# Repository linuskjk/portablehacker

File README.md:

# Portable Hacker

Portable Hacker is a handheld device to test the security of WiFi networks and bluetooth.

## The project is designed to be:
- portable
- modular
- expandable
- easy to modify
- beginner-friendly Hardware

### Why does this exist?
- I created this project to learn how to design PCBs and how to implement communication between microcontrollers.

# Things you need

 - [ESP32 preferably with antenna support](https://de.aliexpress.com/item/1005006140555903.html)
 - [ESP8266 NodeMCU V3](https://de.aliexpress.com/item/1005006889833004.html)
 - [0.91" Oled display (I2C)](https://de.aliexpress.com/item/1005011907100931.html)
 - [Rotary encoder](https://no.rs-online.com/web/p/mechanical-rotary-encoders/1675389)
 - [PCB](pcb/final.kicad_pcb)
 - [2x100k Ohm Resistors](https://www.reichelt.de/de/de/shop/produkt/widerstand_metallschicht_100_kohm_0207_0_6_w_1_-11458)
 - [1x0.1uF capacitor](https://funduinoshop.com/bauelemente/passive-bauelemente/kondensatoren/keramikkondensator-0.1uf-104pf-50v)

# Tools you need
- Soldering Iron
- Solder wire
- 3D-Printer

# Installation

1. Assemble the PCB
2. Solder all components
3. Connect the OLED display
4. Connect the battery to the charger module. (B+/- to charger module and output of that to V+/GND pin) it is not on the pcb on purpose as this saves up a lot of space and still works perfectly fine (even better, as bc of this the battery placement is more flexible. Just click the charger module in the space on the bottom of the case. It fits perfectly and whithholds a lot of strenght.
5. Upload the firmware by uploading v1.ino to the esp32 and the handshakeV2_esp8266.ino to the ESP8266 you can do both by using Arduino IDE
6. Power on the device

## Firmware dependencies

### Arduino / ESP32 firmware

- Adafruit GFX Library
- Adafruit SSD1306
- ESP32Encoder
- BluetoothSerial, WiFi, and Wire are provided by the ESP32 Arduino core

### ESP8266 helper firmware

- ESP8266WiFi, user_interface.h, and the ESP8266 Arduino core

### Python capture tools

- Python 3.9+
- pyserial
- Optional: access to the serial port listed with `--port` or the `PORT` environment variable

The Python capture scripts now auto-detect a connected serial port when possible, but you can still pass a port manually if you want a specific device.

# Features

- ESP32 powered
- OLED UI with menu system
- Rotary encoder navigation
- Battery voltage monitoring
- WiFi network scanner
- Bluetooth scanner
- WiFi deauther
- Bluetooth Spammer
- Modular firmware architecture
- Rechargeable LiPo battery support
- Custom PCB
- 3D printable enclosure support

# Hardware

## Required Components

| Component | Description |
|---|---|
| ESP32 Dev Board | Preferably with external antenna support |
| 0.91\" OLED Display | I2C SSD1306 |
| Rotary Encoder | With push button |
| LiPo Battery | 3.7V rechargeable |
| TP4056 | LiPo charging module |
| 2x 100kΩ Resistors | Battery voltage divider |
| 0.1µF Capacitor | ADC smoothing |
| Custom PCB | Designed in KiCad |

# Battery Measurement Circuit

The battery voltage is measured using a voltage divider connected to GPIO34.

```text
VBAT ── R1 ──+── GPIO34
             |
             +── C1 ── GND
             |
             R2
             |
            GND
```
## Values

| Component | Value |
|---|---|
| R1 | 100kΩ |
| R2 | 100kΩ |
| C1 | 0.1µF |
# Pin Layout

## OLED Display

| OLED Pin | ESP32 Pin |
|---|---|
| SDA | GPIO21 |
| SCL | GPIO22 |
| VCC | 3.3V |
| GND | GND |

---

## Rotary Encoder

| Encoder Pin | ESP32 Pin |
|---|---|
| A | GPIO32 |
| B | GPIO33 |
| SW | GPIO25 |
| + | 3.3V |
| GND | GND |

---

## Battery Monitoring

| Signal | ESP32 Pin |
|---|---|
| BAT_SENSE | GPIO34 |

# Images

## BOM

| Reference | Qty | Value | Description | Price EUR | Pack Info | Link |
|---|---|---|---|---|---|---|
| C1 | 1 | 0.1uF | Unpolarized capacitor | 6.19 | 100 pcs | [Buy](https://amzn.eu/d/09888h7T) |
| R1 R2 | 2 | 100k | Resistors | 8.19 | 50 pcs | [Buy](https://amzn.eu/d/08NQdVll) |
| SW1 | 1 | EC11 Rotary Encoder | Rotary encoder with push button | 2.49 | 1 pc | [Buy](https://arduino-projekte.info/products/ec11-rotary-encoder?srsltid=AfmBOoql9EZHMg89JvVqM8fnVPwwvv0NLhGciYfBVo8YLQL4ypCRxuZV) |
| U2 | 1 | SSD1306 0.91-inch OLED | I2C OLED display 128x32 | 1.35 | 1 pc | [Buy](https://de.aliexpress.com/item/1005011907100931.html) |
| U3 | 1 | ESP32-DevKitC | ESP32 development board | 2.99 | 1 pc | [Buy](https://de.aliexpress.com/item/1005006140555903.html) |
| U4 | 1 | DC-DC Buck Boost 600mA | Step-up/down power module | 0.99 | 1 pc | [Buy](https://de.aliexpress.com/item/1005008878997808.html) |
| U5 | 1 | TP4056 Type-C Charger Module | Li-ion charging module | 0.99 | 1 pc | [Buy](https://de.aliexpress.com/item/1005011840928544.html) |
| U6 | 1 | ESP8266 NodeMCU V3 | WiFi development board | 2.70 | 1 pc | [Buy](https://de.aliexpress.com/item/1005006889833004.html) |
| Battery | 1 | 654060 Li-Po 2000mAh | Lithium polymer battery | 9.90 | 1 pc | [Buy](https://de.aliexpress.com/item/1005011549440731.html) |
| Charger Module | 1 | TP4057 | USB-C charging module | 3.83 | 1 pc | [Buy](https://de.aliexpress.com/item/1005010764961491.html) |

### Total Cost
- Full pack prices: **39.62 EUR**
- Actual project usage cost: **25.46 EUR**

## Authors

- [@linuskjk](https://www.github.com/linuskjk)

## License

See [LICENSE](LICENSE) for the full text.

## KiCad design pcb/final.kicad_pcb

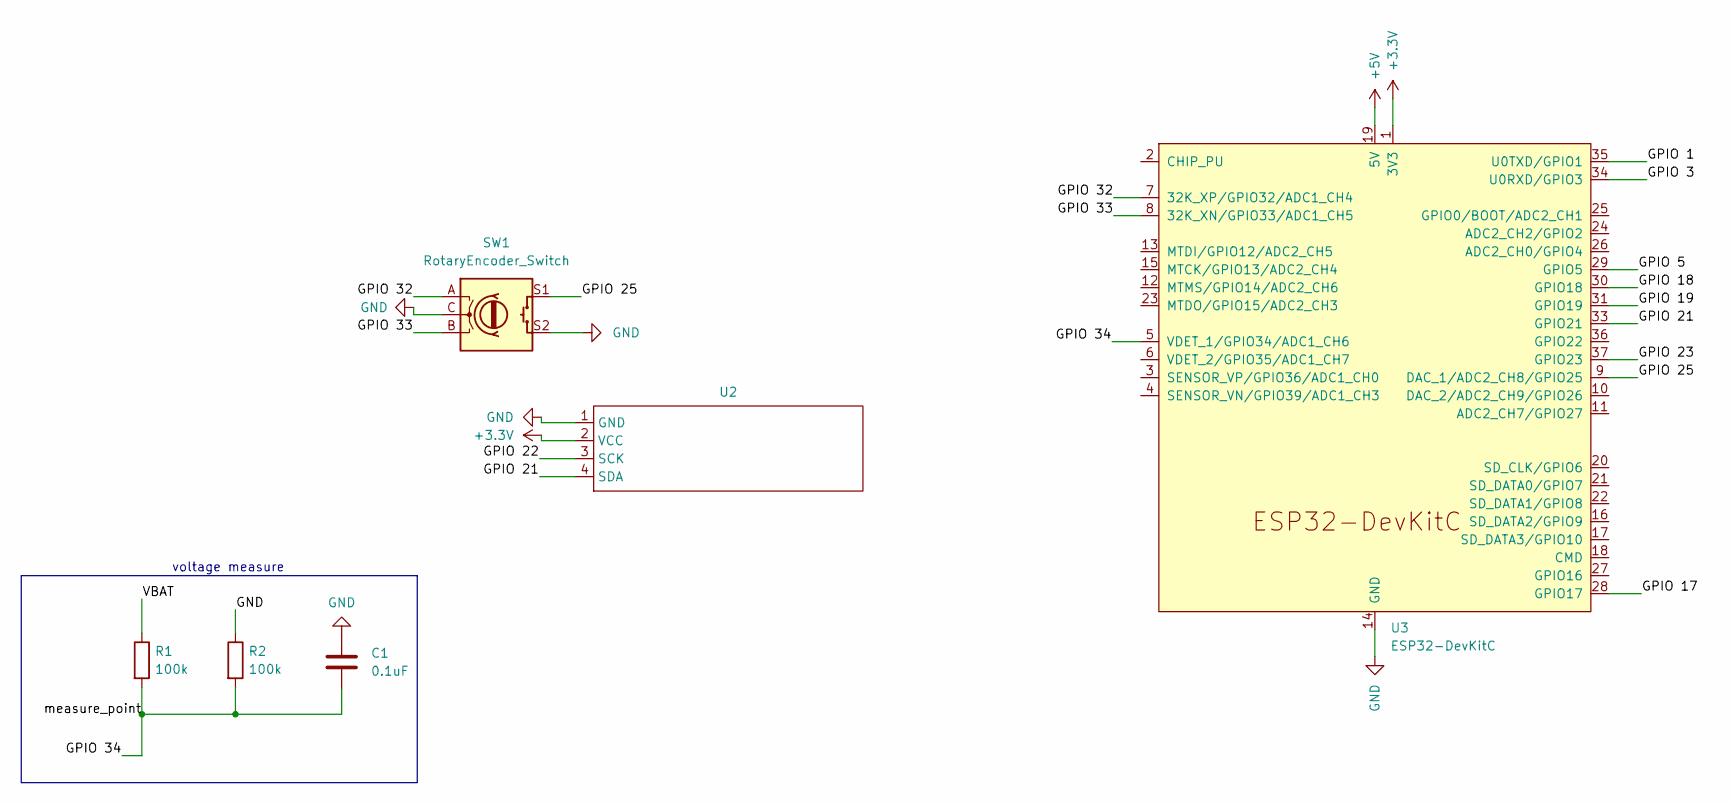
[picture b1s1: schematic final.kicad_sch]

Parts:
C1: 0.1uF; C_Disc_D5.0mm_W2.5mm_P5.00mm
R1, R2: 100k; R_Axial_DIN0207_L6.3mm_D2.5mm_P7.62mm_Horizontal
SW1: RotaryEncoder_Switch; RotaryEncoder_Alps_EC12E-Switch_Vertical_H20mm_CircularMoun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
U2: Untitled
U3: ESP32-DevKitC

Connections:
+3.3V: U2.2 (VCC), U3.1 (3V3)
+5V: U3.19 (5V)
/GPIO 1: U3.35 (U0TXD/GPIO1)
/GPIO 3: U3.34 (U0RXD/GPIO3)
/GPIO 5: U3.29 (GPIO5)
/GPIO 17: U3.28 (GPIO17)
/GPIO 18: U3.30 (GPIO18)
/GPIO 19: U3.31 (GPIO19)
/GPIO 21: U2.4 (SDA), U3.33 (GPIO21)
/GPIO 22: U2.3 (SCK), U3.36 (GPIO22)
/GPIO 23: U3.37 (GPIO23)
/GPIO 25: SW1.S1, U3.9 (DAC_1/ADC2_CH8/GPIO25)
/GPIO 32: SW1.A, U3.7 (32K_XP/GPIO32/ADC1_CH4)
/GPIO 33: SW1.B, U3.8 (32K_XN/GPIO33/ADC1_CH5)
/GPIO 34: C1.2, R1.2, R2.2, U3.5 (VDET_1/GPIO34/ADC1_CH6)
/VBAT: R1.1
GND: C1.1, R2.1, SW1.C, SW1.S2, U2.1 (GND), U3.14 (GND), U3.32 (GND), U3.38 (GND)

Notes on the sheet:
voltage measure

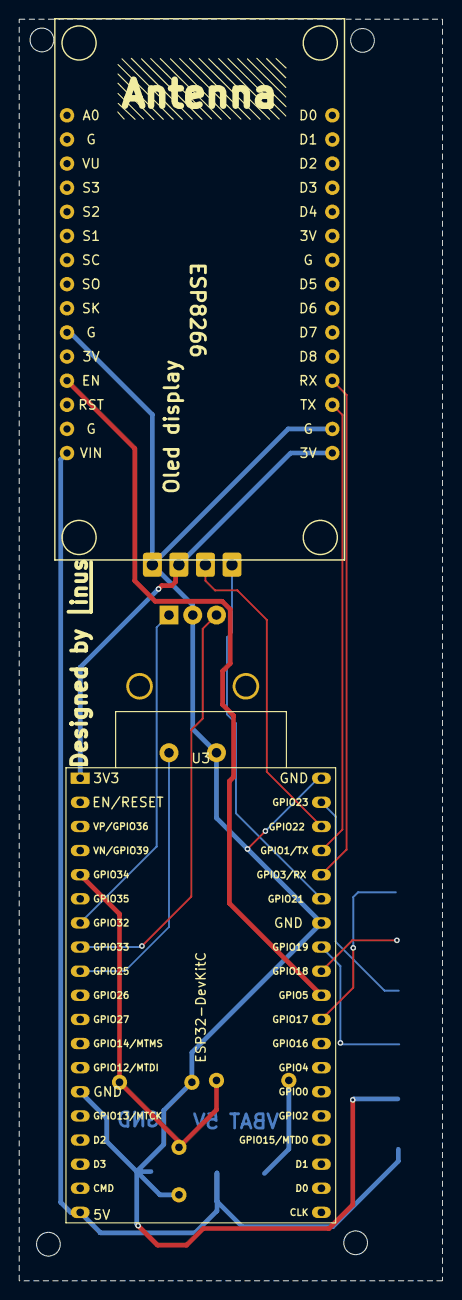
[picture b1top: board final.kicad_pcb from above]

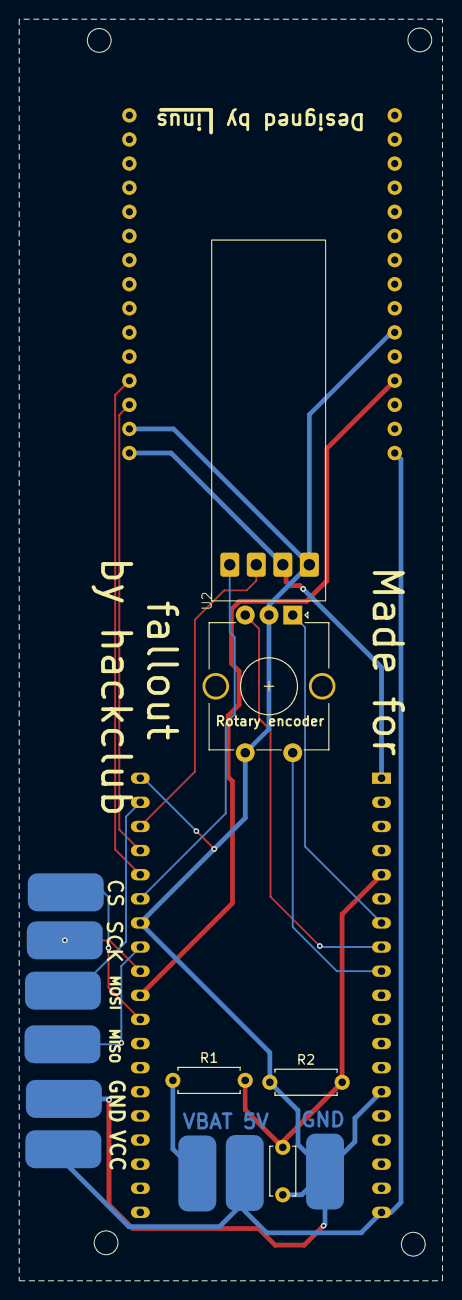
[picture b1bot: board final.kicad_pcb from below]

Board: 2 copper layers, 44.6 x 132.8 mm, 6 parts (5 on the bottom side), 8 nets.

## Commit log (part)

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2026-05-14 Initial commit: Add all Portable Hacker project files
2026-05-14 Remove large CASE/case_model.f3d file
2026-05-14 Restore CASE/case_model.f3d file to repository
2026-05-14 Add Git LFS for large files, restore case_model.f3d, and add project README
2026-05-14 Configure Git LFS for case_model.f3d - LFS pointer only
2026-05-14 Revise README with detailed project and hardware info
    Expanded project description and added detailed hardware requirements, installation steps, and future plans.
2026-05-14 Revise hardware list in README
    Updated hardware requirements and added new components with links.
2026-05-14 Update firmware upload instructions in README
    Clarified steps for uploading firmware in README.
2026-05-14 Revise README for clarity and formatting
    Updated description for firmware UI and adjusted section header.
2026-05-14 Revise README
2026-05-16 Update README with project design and purpose
    Added sections on project design and purpose.
2026-05-16 Add images section to README
    Added images to the README for better visualization.
2026-05-16 Add image to README for Portable Hacker
    Added an image to the README for visual reference.
2026-05-16 Replace all repo content with case, docs, firmware, pcb, zine folders and README with LFS for model files
2026-05-16 Rename folders to lowercase: CASE -> case, PCB -> pcb, ZINE -> zine
2026-05-17 Refactor BLE advertising interval settings
2026-05-17 Fixed bugs in captivePortal.ino
2026-05-17 Refactor handshakeV4.ino
    Removed unnecessary code and improved code clarity.
2026-05-17 Refactor Serial command handling in loop
2026-05-17 Refactor WiFi packet handling in firmware
2026-05-22 Revise BOM format to add price and pack info
    Updated BOM to include pricing and additional details.
2026-05-22 Add images to the README file
2026-05-22 Fix serial tools and repo docs
2026-05-22 Fix LFS tracking rules
2026-05-22 Add fully assembled Fusion exports
2026-05-22 Add fully assembled STEP export
2026-05-23 Update battery connection instructions in README
    Clarified instructions for connecting the battery to the charger module and voltage regulator.
2026-05-23 Reupload rebuilt case assemblies
2026-05-23 Reupload updated case model assets
2026-05-25 Create test
2026-05-25 Replace old image with new image in README
    Updated image link in README and added a new image.
2026-05-25 Add ESP8266 deauthentication attack functionality
2026-05-25 Rename firmware/esp8266_v1.ino to firmware/esp8266_v1/esp8266_v1.ino
2026-05-25 Add main firmware for ESP32 with multiple features
    This commit introduces the main firmware for the ESP32 device, implementing various functionalities such as BLE spam, twin attack, and D-Auth capabilities. It includes setup for display, encoder hand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
2026-05-25 Add BOM section to README with component details
    Added Bill of Materials (BOM) section with components and pricing.
2026-06-01 Update battery connection instructions in README
    Clarified instructions for connecting the battery and charger module in the README.
2026-06-01 Update bom.csv with new charger module and totals
    Added a new charger module and updated total price.
2026-06-01 Add TP4057 charger module and update costs
    Updated total costs and added TP4057 charger module to the components list.

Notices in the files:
README.md:
License:
[MIT License](https://choosealicense.com/licenses/mit/)
